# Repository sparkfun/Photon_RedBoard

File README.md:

SparkFun Photon RedBoard
========================================

[*SparkFun Photon RedBoard (DEV-13321)*](https://www.sparkfun.com/products/13321)

The SparkFun Photon RedBoard is a Particle Cloud-compatible WiFi development board. It can be programmed over-the-air, using Particle's Build IDE. It's like a Photon, but Arduino-shaped and red!

Repository Contents
-------------------

* **/Documentation** - Data sheets, additional product information
* **/Hardware** - Eagle design files (.brd, .sch)
* **/Production** - Production panel files (.brd)

Documentation
--------------
* **[Hookup Guide](https://learn.sparkfun.com/tutorials/photon-redboard-hookup-guide)** - Basic hookup guide for the SparkFun Photon RedBoard.
* **[Experiment Guide](https://learn.sparkfun.com/tutorials/photon-redboard-hookup-guide)** - Experiment guide for the SparkFun Photon RedBoard to send and receive data over WiFi.
* **[SparkFun Fritzing repo](https://github.com/sparkfun/Fritzing_Parts)** - Fritzing diagrams for SparkFun products.
* **[SparkFun 3D Model repo](https://github.com/sparkfun/3D_Models)** - 3D models of SparkFun products. 

Product Versions
----------------
* [DEV-13321](https://www.sparkfun.com/products/13321) - **Photon RedBoard**: Initial release of the SparkFun Photon RedBoard.
* [KIT-13320](https://www.sparkfun.com/products/13320) - **SparkFun Inventor's Kit for Photon**: A SparkFun Inventor's Kit based around the Photon RedBoard.

Version History
---------------
* [V_1.0](https://github.com/sparkfun/Photon_RedBoard/tree/V_1.0) - Initial hardware release - 1.0.

License Information
-------------------

This product is _**open source**_! 

Please review the LICENSE.md file for license information. 

If you have any questions or concerns on licensing, please contact techsupport@sparkfun.com.

Distributed as-is; no warranty is given.

- Your friends at SparkFun.

_<COLLABORATION CREDIT>_

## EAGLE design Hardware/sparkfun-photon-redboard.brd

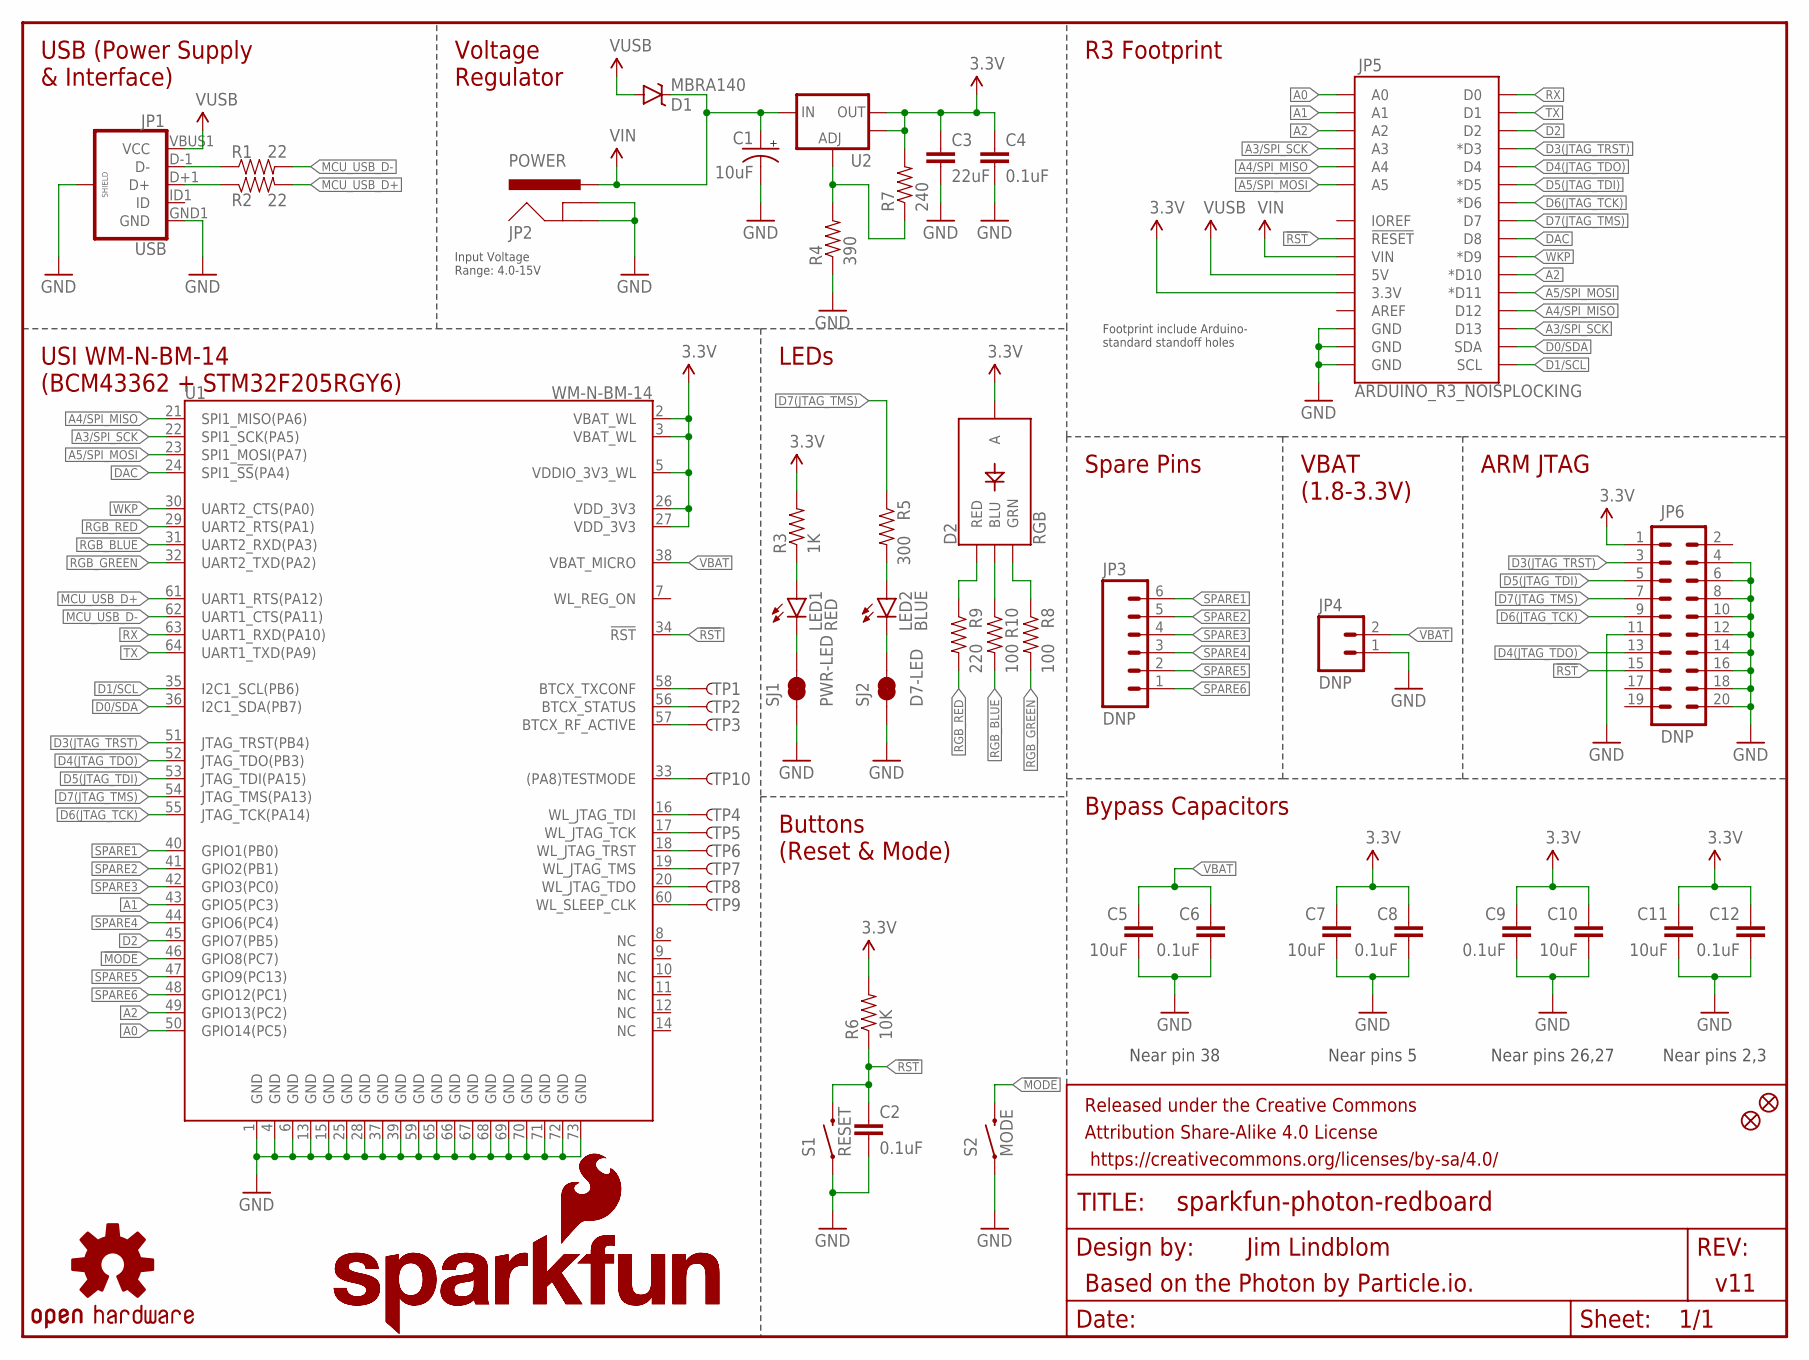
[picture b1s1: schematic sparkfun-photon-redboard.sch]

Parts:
C1: 10uF; EIA3216
C2, C4, C6, C8, C9, C12: 0.1uF; 0603-CAP
C3: 22uF; 0805
C5, C7, C10, C11: 10uF; 0603-CAP
D1: MBRA140; SMA-DIODE
D2: RGB; P-LCC-4-3
FID1, FID2: FIDUCIAL1X2; FIDUCIAL-1X2
FRAME1: FRAME-LETTER; CREATIVE_COMMONS
JP1: USB; USB-B-MICRO-SMD_V03
JP2: POWER; POWER_JACK_PTH_LOCK
JP3: DNP; 1X06
JP4: DNP; 1X02
JP5: ARDUINO_R3_NOISPLOCKING; ARDUINO_R3_NOISP_LOCKING
JP6: DNP; 2X10
LED1: RED; LED-1206
LED2: BLUE; LED-1206
LOGO1: OSHW-LOGOM; OSHW-LOGO-M
LOGO2: SFE_LOGO_NAME_FLAME.2_INCH; SFE_LOGO_NAME_FLAME_.2
LOGO3: SFE_LOGO_NAME_FLAME.4_INCH; SFE_LOGO_NAME_FLAME_.4
R1, R2: 22; 0603-RES
R3: 1K; 0603-RES
R4: 390; 0603-RES
R5: 300; 0603-RES
R6: 10K; 0603-RES
R7: 240; 0603-RES
R8: 100; 0603-RES
R9: 220; 0603
R10: 100; 0603
S1: RESET; TACTILE-PTH
S2: MODE; TACTILE-PTH
SJ1: PWR-LED; PAD-JUMPER-2-NC_BY_TRACE_YES_SILK
SJ2: D7-LED; PAD-JUMPER-2-NC_BY_TRACE_YES_SILK
TP1, TP2, TP3, TP4, TP5, TP6, TP7, TP8, TP9, TP10: TEST-POINTTP_15TH_THRU; TP_15TH
U1: WM-N-BM-14
U2: V_REG_LM1117SOT223; SOT223

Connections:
3.3V: C3.1, C4.1, C7.1, C8.1, C9.1, C10.1, C11.1, C12.1, D2.4 (A), JP5.3.3V, JP6.1, R3.2, R6.2, R7.2, U1.2 (VBAT_WL), U1.3 (VBAT_WL), U1.5 (VDDIO_3V3_WL), U1.26 (VDD_3V3), U1.27 (VDD_3V3), U2.2 (OUT), U2.4 (OUT)
!MODE: S2.3 (2), U1.46 (GPIO8(PC7))
!RST: C2.1, JP5.RESET@1 (!RESET!), JP6.15, R6.1, S1.3 (2), U1.34 (!RST!)
A0: JP5.A0, U1.50 (GPIO14(PC5))
A1: JP5.A1, U1.43 (GPIO5(PC3))
A2: JP5.A2, JP5.D10 (*D10), U1.49 (GPIO13(PC2))
A3/SPI_SCK: JP5.A3, JP5.D13, U1.22 (SPI1_SCK(PA5))
A4/SPI_MISO: JP5.A4, JP5.D12, U1.21 (SPI1_MISO(PA6))
A5/SPI_MOSI: JP5.A5, JP5.D11 (*D11), U1.23 (SPI1_MOSI(PA7))
BTCX_RF_ACTIVE: TP3.P$1, U1.57 (BTCX_RF_ACTIVE)
BTCX_STATUS: TP2.P$1, U1.56 (BTCX_STATUS)
BTCX_TXCONF: TP1.P$1, U1.58 (BTCX_TXCONF)
D0/SDA: JP5.SDA, U1.36 (I2C1_SDA(PB7))
D1/SCL: JP5.SCL, U1.35 (I2C1_SCL(PB6))
D2: JP5.D2, U1.45 (GPIO7(PB5))
D3(JTAG_TRST): JP5.D3 (*D3), JP6.3, U1.51 (JTAG_TRST(PB4))
D4(JTAG_TDO): JP5.D4, JP6.13, U1.52 (JTAG_TDO(PB3))
D5(JTAG_TDI): JP5.D5 (*D5), JP6.5, U1.53 (JTAG_TDI(PA15))
D6(JTAG_TCK): JP5.D6 (*D6), JP6.9, U1.55 (JTAG_TCK(PA14))
D7(JTAG_TMS): JP5.D7, JP6.7, R5.1, U1.54 (JTAG_TMS(PA13))
D+: JP1.D+1 (D+), R2.1
D-: JP1.D-1 (D-), R1.1
DAC: JP5.D8, U1.24 (SPI1_!SS!(PA4))
GND: C1.C (-), C2.2, C3.2, C4.2, C5.2, C6.2, C7.2, C8.2, C9.2, C10.2, C11.2, C12.2, JP1.GND1 (GND), JP1.SHIELD1 (SHIELD), JP1.SHIELD2 (SHIELD), JP1.SHIELD3 (SHIELD), JP2.GND, JP2.GNDBREAK, JP4.1, JP5.GND@1 (GND), JP5.GND@2 (GND), JP5.GND@3 (GND), JP6.4, JP6.6, JP6.8, JP6.10, JP6.11, JP6.12, JP6.14, JP6.16, JP6.18, JP6.20, R4.1, S1.1, S2.1, SJ1.1, SJ2.1, U1.1 (GND), U1.4 (GND), U1.6 (GND), U1.13 (GND), U1.15 (GND), U1.25 (GND), U1.28 (GND), U1.37 (GND), U1.39 (GND), U1.59 (GND), U1.65 (GND), U1.66 (GND), U1.67 (GND), U1.68 (GND), U1.69 (GND), U1.70 (GND), U1.71 (GND), U1.72 (GND), U1.73 (GND)
MCU_USB_D+: R2.2, U1.61 (UART1_RTS(PA12))
MCU_USB_D-: R1.2, U1.62 (UART1_CTS(PA11))
unnamed: TP10.P$1, U1.33 ((PA8)TESTMODE)
unnamed: LED1.C, SJ1.2
unnamed: D2.2 (GRN), R8.1
unnamed: D2.1 (RED), R9.1
unnamed: LED1.A, R3.1
unnamed: LED2.A, R5.2
unnamed: LED2.C, SJ2.2
unnamed: D2.3 (BLU), R10.1
unnamed: R4.2, R7.1, U2.1 (ADJ)
RGB_BLUE: R10.2, U1.31 (UART2_RXD(PA3))
RGB_GREEN: R8.2, U1.32 (UART2_TXD(PA2))
RGB_RED: R9.2, U1.29 (UART2_RTS(PA1))
RX: JP5.D0, U1.63 (UART1_RXD(PA10))
SPARE1: JP3.6, U1.40 (GPIO1(PB0))
SPARE2: JP3.5, U1.41 (GPIO2(PB1))
SPARE3: JP3.4, U1.42 (GPIO3(PC0))
SPARE4: JP3.3, U1.44 (GPIO6(PC4))
SPARE5: JP3.2, U1.47 (GPIO9(PC13))
SPARE6: JP3.1, U1.48 (GPIO12(PC1))
TX: JP5.D1, U1.64 (UART1_TXD(PA9))
VBAT: C5.1, C6.1, JP4.2, U1.38 (VBAT_MICRO)
VIN: C1.A (+), D1.C, JP2.PWR, JP5.VIN, U2.3 (IN)
VUSB: D1.A, JP1.VBUS1 (VCC), JP5.5V
WKP: JP5.D9 (*D9), U1.30 (UART2_CTS(PA0))
WL_JTAG_TCK: TP5.P$1, U1.17 (WL_JTAG_TCK)
WL_JTAG_TDI: TP4.P$1, U1.16 (WL_JTAG_TDI)
WL_JTAG_TDO: TP8.P$1, U1.20 (WL_JTAG_TDO)
WL_JTAG_TMS: TP7.P$1, U1.19 (WL_JTAG_TMS)
WL_JTAG_TRST: TP6.P$1, U1.18 (WL_JTAG_TRST)
WL_SLEEP_CLK: TP9.P$1, U1.60 (WL_SLEEP_CLK)

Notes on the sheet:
Near pin 38
Near pins 26,27
Near pins 5
Near pins 2,3
Voltage Regulator
USB (Power Supply & Interface)
R3 Footprint
Spare Pins
VBAT (1.8-3.3V)
ARM JTAG
Bypass Capacitors
LEDs
Buttons (Reset & Mode)
USI WM-N-BM-14 (BCM43362 + STM32F205RGY6)
Based on the Photon by Particle.io.
Jim Lindblom
v11
Input Voltage Range: 4.0-15V
Footprint include Arduino- standard standoff holes

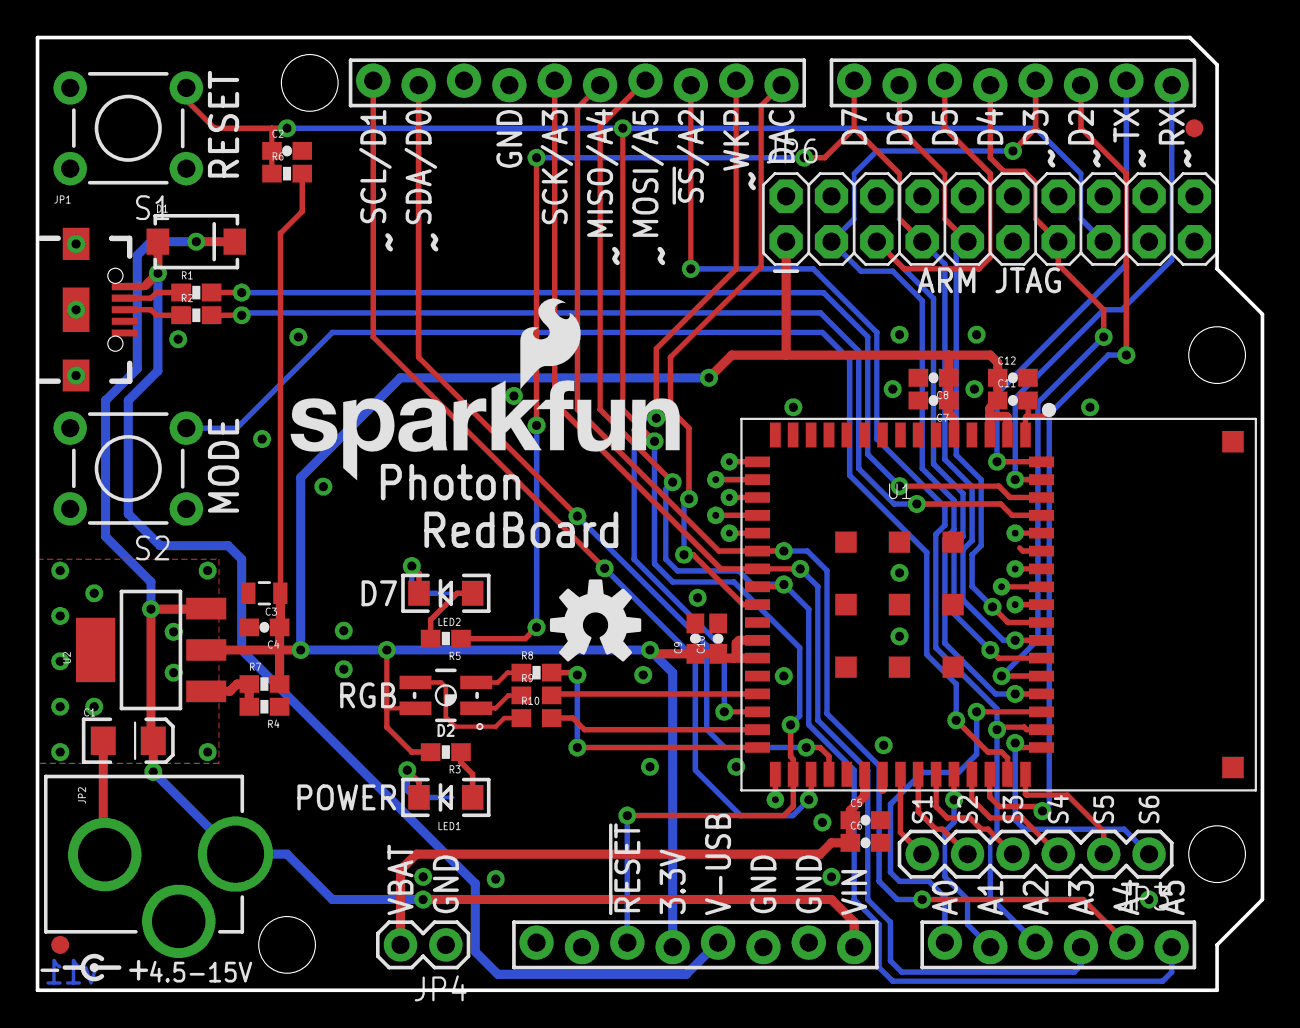
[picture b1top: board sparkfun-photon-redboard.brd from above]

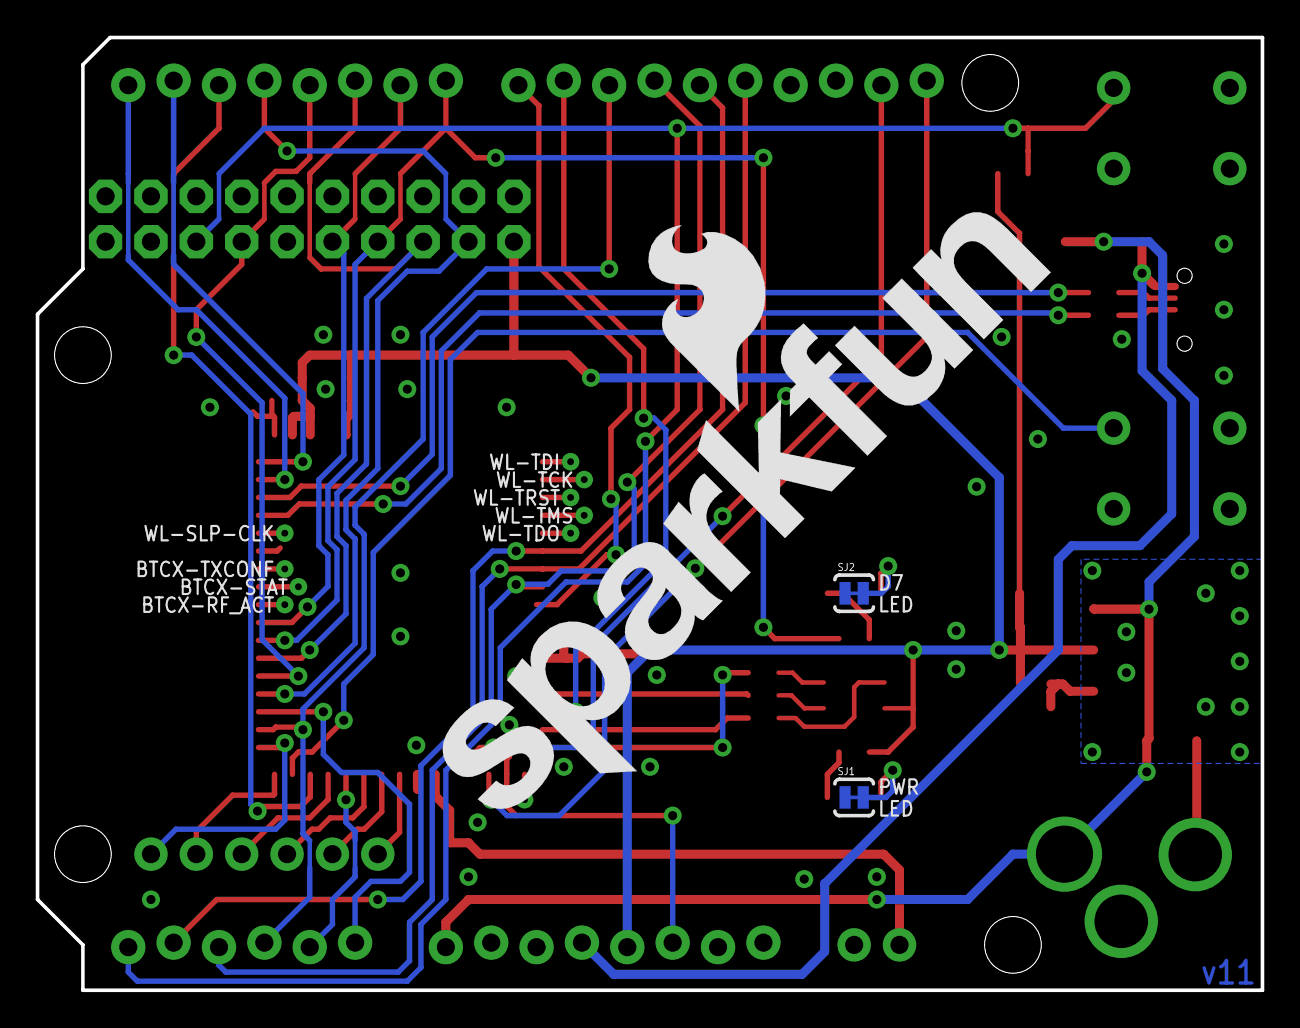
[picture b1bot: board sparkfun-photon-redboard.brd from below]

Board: 2 copper layers, 68.6 x 53.3 mm, 54 parts (3 on the bottom side), 56 nets.

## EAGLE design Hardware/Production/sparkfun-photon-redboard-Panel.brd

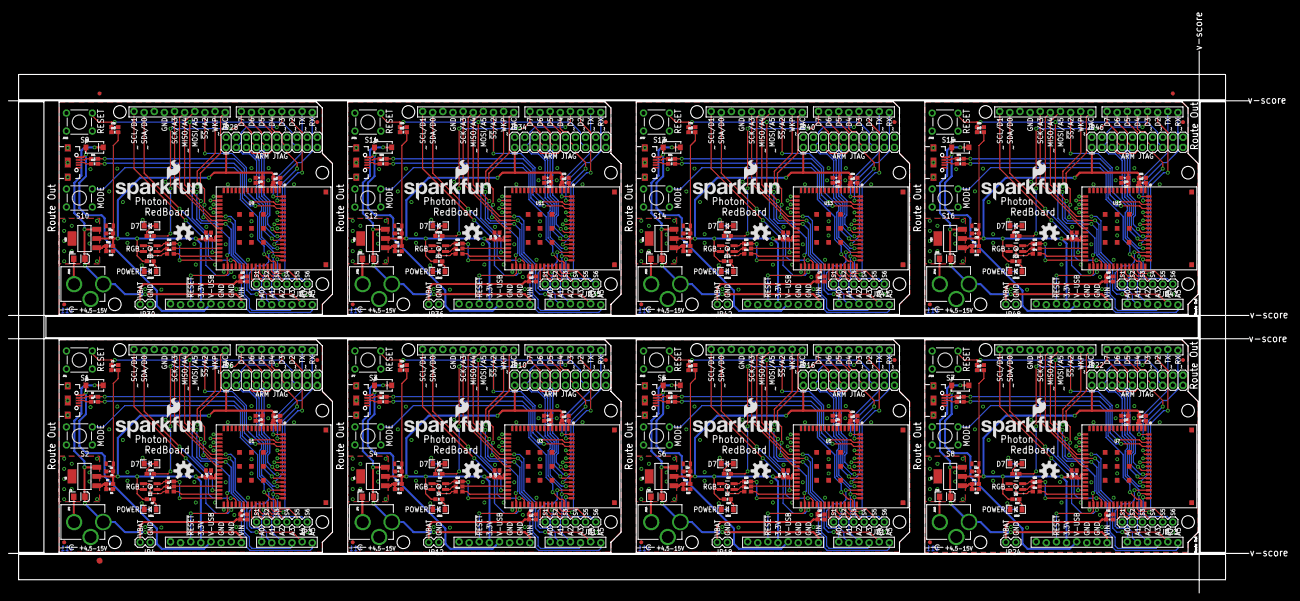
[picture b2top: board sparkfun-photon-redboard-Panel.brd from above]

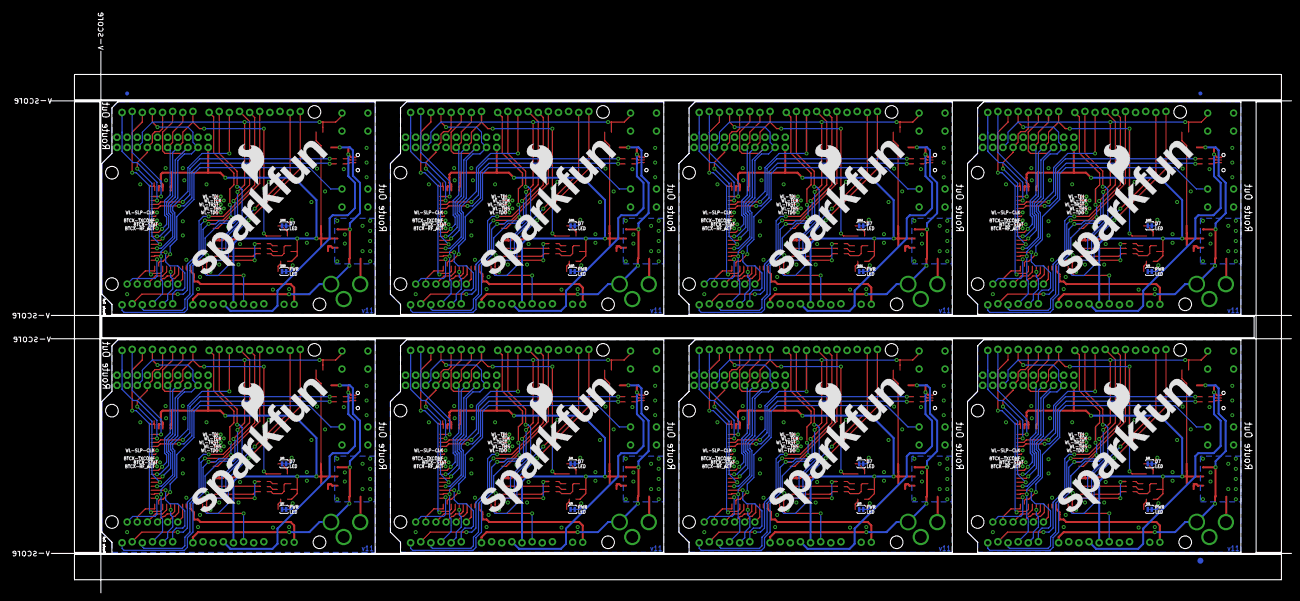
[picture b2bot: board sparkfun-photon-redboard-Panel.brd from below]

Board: 2 copper layers, 321.9 x 146.6 mm, 430 parts (27 on the bottom side), 448 nets.

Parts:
C1, C14, C26, C38, C50, C62, C74, C86: 10uF; EIA3216
C2, C4, C6, C8, C9, C12, C13, C16, C21, C22, C23, C24, C25, C28, C33, C34, C35, C36, C37, C40, C45, C46, C47, C48, C49, C52, C57, C58, C59, C60, C61, C64, C69, C70, C71, C72, C73, C76, C81, C82, C83, C84, C85, C88, C93, C94, C95, C96: 0.1uF; 0603-CAP
C3, C15, C27, C39, C51, C63, C75, C87: 22uF; 0805
C5, C7, C10, C11, C17, C18, C19, C20, C29, C30, C31, C32, C41, C42, C43, C44, C53, C54, C55, C56, C65, C66, C67, C68, C77, C78, C79, C80, C89, C90, C91, C92: 10uF; 0603-CAP
D1, D3, D5, D7, D9, D11, D13, D15: MBRA140; SMA-DIODE
D2, D4, D6, D8, D10, D12, D14, D16: RGB; P-LCC-4-3
E$1, E$2, E$3, E$4: FIDUCIAL-1X2
E$5, E$6: FIDUCIAL-1.5X3
FID1, FID2, FID3, FID4, FID5, FID6, FID7, FID8, FID9, FID10, FID11, FID12, FID13, FID14, FID15, FID16: FIDUCIAL1X2; FIDUCIAL-1X2
JP1, JP7, JP13, JP19, JP25, JP31, JP37, JP43: USB; USB-B-MICRO-SMD_V03
JP2, JP8, JP14, JP20, JP26, JP32, JP38, JP44: POWER; POWER_JACK_PTH_LOCK
JP3, JP11, JP17, JP23, JP29, JP35, JP41, JP47: DNP; 1X06
JP4, JP12, JP18, JP24, JP30, JP36, JP42, JP48: DNP; 1X02
JP5, JP9, JP15, JP21, JP27, JP33, JP39, JP45: ARDUINO_R3_NOISPLOCKING; ARDUINO_R3_NOISP_LOCKING
JP6, JP10, JP16, JP22, JP28, JP34, JP40, JP46: DNP; 2X10
LED1, LED4, LED6, LED8, LED10, LED12, LED14, LED16: RED; LED-1206
LED2, LED3, LED5, LED7, LED9, LED11, LED13, LED15: BLUE; LED-1206
LOGO1, LOGO5, LOGO8, LOGO11, LOGO14, LOGO17, LOGO20, LOGO23: OSHW-LOGOM; OSHW-LOGO-M
LOGO2, LOGO4, LOGO7, LOGO10, LOGO13, LOGO16, LOGO19, LOGO22: SFE_LOGO_NAME_FLAME.2_INCH; SFE_LOGO_NAME_FLAME_.2
LOGO3, LOGO6, LOGO9, LOGO12, LOGO15, LOGO18, LOGO21, LOGO24: SFE_LOGO_NAME_FLAME.4_INCH; SFE_LOGO_NAME_FLAME_.4
R1, R2, R11, R12, R21, R22, R31, R32, R41, R42, R51, R52, R61, R62, R71, R72: 22; 0603-RES
R3, R18, R28, R38, R48, R58, R68, R78: 1K; 0603-RES
R4, R19, R29, R39, R49, R59, R69, R79: 390; 0603-RES
R5, R17, R27, R37, R47, R57, R67, R77: 300; 0603-RES
R6, R13, R23, R33, R43, R53, R63, R73: 10K; 0603-RES
R7, R20, R30, R40, R50, R60, R70, R80: 240; 0603-RES
R8, R16, R26, R36, R46, R56, R66, R76: 100; 0603-RES
R9, R15, R25, R35, R45, R55, R65, R75: 220; 0603
R10, R14, R24, R34, R44, R54, R64, R74: 100; 0603
S1, S3, S5, S7, S9, S11, S13, S15: RESET; TACTILE-PTH
S2, S4, S6, S8, S10, S12, S14, S16: MODE; TACTILE-PTH
SJ1, SJ3, SJ5, SJ7, SJ9, SJ11, SJ13, SJ15: PWR-LED; PAD-JUMPER-2-NC_BY_TRACE_YES_SILK
SJ2, SJ4, SJ6, SJ8, SJ10, SJ12, SJ14, SJ16: D7-LED; PAD-JUMPER-2-NC_BY_TRACE_YES_SILK
TP1, TP2, TP3, TP4, TP5, TP6, TP7, TP8, TP9, TP10, TP11, TP12, TP13, TP14, TP15, TP16, TP17, TP18, TP19, TP20, TP21, TP22, TP23, TP24, TP25, TP26, TP27, TP28, TP29, TP30, TP31, TP32, TP33, TP34, TP35, TP36, TP37, TP38, TP39, TP40, TP41, TP42, TP43, TP44, TP45, TP46, TP47, TP48, TP49, TP50, TP51, TP52, TP53, TP54, TP55, TP56, TP57, TP58, TP59, TP60, TP61, TP62, TP63, TP64, TP65, TP66, TP67, TP68, TP69, TP70, TP71, TP72, TP73, TP74, TP75, TP76, TP77, TP78, TP79, TP80: TEST-POINTTP_15TH_THRU; TP_15TH
U1, U3, U5, U7, U9, U11, U13, U15: WM-N-BM-14
U2, U4, U6, U8, U10, U12, U14, U16: SOT223

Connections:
3.3V: C3.1, C4.1, C7.1, C8.1, C9.1, C10.1, C11.1, C12.1, D2.4, JP5.3.3V, JP6.1, R3.2, R6.2, R7.2, U1.2, U1.3, U1.5, U1.26, U1.27, U2.2, U2.4
3.3V1: C13.1, C15.1, C18.1, C19.1, C20.1, C22.1, C23.1, C24.1, D4.4, JP9.3.3V, JP10.1, R13.2, R18.2, R20.2, U3.2, U3.3, U3.5, U3.26, U3.27, U4.2, U4.4
3.3V2: C25.1, C27.1, C30.1, C31.1, C32.1, C34.1, C35.1, C36.1, D6.4, JP15.3.3V, JP16.1, R23.2, R28.2, R30.2, U5.2, U5.3, U5.5, U5.26, U5.27, U6.2, U6.4
3.3V3: C37.1, C39.1, C42.1, C43.1, C44.1, C46.1, C47.1, C48.1, D8.4, JP21.3.3V, JP22.1, R33.2, R38.2, R40.2, U7.2, U7.3, U7.5, U7.26, U7.27, U8.2, U8.4
3.3V4: C49.1, C51.1, C54.1, C55.1, C56.1, C58.1, C59.1, C60.1, D10.4, JP27.3.3V, JP28.1, R43.2, R48.2, R50.2, U9.2, U9.3, U9.5, U9.26, U9.27, U10.2, U10.4
3.3V5: C61.1, C63.1, C66.1, C67.1, C68.1, C70.1, C71.1, C72.1, D12.4, JP33.3.3V, JP34.1, R53.2, R58.2, R60.2, U11.2, U11.3, U11.5, U11.26, U11.27, U12.2, U12.4
3.3V6: C73.1, C75.1, C78.1, C79.1, C80.1, C82.1, C83.1, C84.1, D14.4, JP39.3.3V, JP40.1, R63.2, R68.2, R70.2, U13.2, U13.3, U13.5, U13.26, U13.27, U14.2, U14.4
3.3V7: C85.1, C87.1, C90.1, C91.1, C92.1, C94.1, C95.1, C96.1, D16.4, JP45.3.3V, JP46.1, R73.2, R78.2, R80.2, U15.2, U15.3, U15.5, U15.26, U15.27, U16.2, U16.4
!MODE: S2.3, U1.46
!MODE1: S4.3, U3.46
!MODE2: S6.3, U5.46
!MODE3: S8.3, U7.46
!MODE4: S10.3, U9.46
!MODE5: S12.3, U11.46
!MODE6: S14.3, U13.46
!MODE7: S16.3, U15.46
!RST: C2.1, JP5.RESET@1, JP6.15, R6.1, S1.3, U1.34
!RST1: C16.1, JP9.RESET@1, JP10.15, R13.1, S3.3, U3.34
!RST2: C28.1, JP15.RESET@1, JP16.15, R23.1, S5.3, U5.34
!RST3: C40.1, JP21.RESET@1, JP22.15, R33.1, S7.3, U7.34
!RST4: C52.1, JP27.RESET@1, JP28.15, R43.1, S9.3, U9.34
!RST5: C64.1, JP33.RESET@1, JP34.15, R53.1, S11.3, U11.34
!RST6: C76.1, JP39.RESET@1, JP40.15, R63.1, S13.3, U13.34
!RST7: C88.1, JP45.RESET@1, JP46.15, R73.1, S15.3, U15.34
A0: JP5.A0, U1.50
A1: JP5.A1, U1.43
A2: JP5.A2, JP5.D10, U1.49
A3: JP9.A2, JP9.D10, U3.49
A3/SPI_SCK: JP5.A3, JP5.D13, U1.22
A3/SPI_SCK1: JP9.A3, JP9.D13, U3.22
A3/SPI_SCK2: JP15.A3, JP15.D13, U5.22
A3/SPI_SCK3: JP21.A3, JP21.D13, U7.22
A3/SPI_SCK4: JP27.A3, JP27.D13, U9.22
A3/SPI_SCK5: JP33.A3, JP33.D13, U11.22
A3/SPI_SCK6: JP39.A3, JP39.D13, U13.22
A3/SPI_SCK7: JP45.A3, JP45.D13, U15.22
A4: JP9.A1, U3.43
A4/SPI_MISO: JP5.A4, JP5.D12, U1.21
A4/SPI_MISO1: JP9.A4, JP9.D12, U3.21
A4/SPI_MISO2: JP15.A4, JP15.D12, U5.21
A4/SPI_MISO3: JP21.A4, JP21.D12, U7.21
A4/SPI_MISO4: JP27.A4, JP27.D12, U9.21
A4/SPI_MISO5: JP33.A4, JP33.D12, U11.21
A4/SPI_MISO6: JP39.A4, JP39.D12, U13.21
A4/SPI_MISO7: JP45.A4, JP45.D12, U15.21
A5: JP9.A0, U3.50
A5/SPI_MOSI: JP5.A5, JP5.D11, U1.23
A5/SPI_MOSI1: JP9.A5, JP9.D11, U3.23
A5/SPI_MOSI2: JP15.A5, JP15.D11, U5.23
A5/SPI_MOSI3: JP21.A5, JP21.D11, U7.23
A5/SPI_MOSI4: JP27.A5, JP27.D11, U9.23
A5/SPI_MOSI5: JP33.A5, JP33.D11, U11.23
A5/SPI_MOSI6: JP39.A5, JP39.D11, U13.23
A5/SPI_MOSI7: JP45.A5, JP45.D11, U15.23
A6: JP15.A2, JP15.D10, U5.49
A7: JP15.A1, U5.43
A8: JP15.A0, U5.50
A9: JP21.A2, JP21.D10, U7.49
A10: JP21.A1, U7.43
A11: JP21.A0, U7.50
A12: JP27.A2, JP27.D10, U9.49
A13: JP27.A1, U9.43
A14: JP27.A0, U9.50
A15: JP33.A2, JP33.D10, U11.49
A16: JP33.A1, U11.43
A17: JP33.A0, U11.50
A18: JP39.A2, JP39.D10, U13.49
A19: JP39.A1, U13.43
A20: JP39.A0, U13.50
A21: JP45.A2, JP45.D10, U15.49
A22: JP45.A1, U15.43
A23: JP45.A0, U15.50
BTCX_RF_ACTIVE: TP3.P$1, U1.57
BTCX_RF_ACTIVE1: TP11.P$1, U3.57
BTCX_RF_ACTIVE2: TP21.P$1, U5.57
BTCX_RF_ACTIVE3: TP31.P$1, U7.57
BTCX_RF_ACTIVE4: TP41.P$1, U9.57
BTCX_RF_ACTIVE5: TP51.P$1, U11.57
BTCX_RF_ACTIVE6: TP61.P$1, U13.57
BTCX_RF_ACTIVE7: TP71.P$1, U15.57
BTCX_STATUS: TP2.P$1, U1.56
BTCX_STATUS1: TP13.P$1, U3.56
BTCX_STATUS2: TP23.P$1, U5.56
BTCX_STATUS3: TP33.P$1, U7.56
BTCX_STATUS4: TP43.P$1, U9.56
BTCX_STATUS5: TP53.P$1, U11.56
BTCX_STATUS6: TP63.P$1, U13.56
BTCX_STATUS7: TP73.P$1, U15.56
BTCX_TXCONF: TP1.P$1, U1.58
BTCX_TXCONF1: TP12.P$1, U3.58
BTCX_TXCONF2: TP22.P$1, U5.58
BTCX_TXCONF3: TP32.P$1, U7.58
BTCX_TXCONF4: TP42.P$1, U9.58
BTCX_TXCONF5: TP52.P$1, U11.58
BTCX_TXCONF6: TP62.P$1, U13.58
BTCX_TXCONF7: TP72.P$1, U15.58
D0/SDA: JP5.SDA, U1.36
D0/SDA1: JP9.SDA, U3.36
D0/SDA2: JP15.SDA, U5.36
D0/SDA3: JP21.SDA, U7.36
D0/SDA4: JP27.SDA, U9.36
D0/SDA5: JP33.SDA, U11.36
D0/SDA6: JP39.SDA, U13.36
D0/SDA7: JP45.SDA, U15.36
D1: JP9.D2, U3.45
D1/SCL: JP5.SCL, U1.35
D1/SCL1: JP9.SCL, U3.35
D1/SCL2: JP15.SCL, U5.35
D1/SCL3: JP21.SCL, U7.35
D1/SCL4: JP27.SCL, U9.35
D1/SCL5: JP33.SCL, U11.35
D1/SCL6: JP39.SCL, U13.35
D1/SCL7: JP45.SCL, U15.35
D2: JP5.D2, U1.45
D3: JP15.D2, U5.45
D3(JTAG_TRST): JP5.D3, JP6.3, U1.51
D3(JTAG_TRST)1: JP9.D3, JP10.3, U3.51
D3(JTAG_TRST)2: JP15.D3, JP16.3, U5.51
D3(JTAG_TRST)3: JP21.D3, JP22.3, U7.51
D3(JTAG_TRST)4: JP27.D3, JP28.3, U9.51
D3(JTAG_TRST)5: JP33.D3, JP34.3, U11.51
D3(JTAG_TRST)6: JP39.D3, JP40.3, U13.51
D3(JTAG_TRST)7: JP45.D3, JP46.3, U15.51
D4: JP21.D2, U7.45
D4(JTAG_TDO): JP5.D4, JP6.13, U1.52
D4(JTAG_TDO)1: JP9.D4, JP10.13, U3.52
D4(JTAG_TDO)2: JP15.D4, JP16.13, U5.52
D4(JTAG_TDO)3: JP21.D4, JP22.13, U7.52
D4(JTAG_TDO)4: JP27.D4, JP28.13, U9.52
D4(JTAG_TDO)5: JP33.D4, JP34.13, U11.52
D4(JTAG_TDO)6: JP39.D4, JP40.13, U13.52
D4(JTAG_TDO)7: JP45.D4, JP46.13, U15.52
D5: JP27.D2, U9.45
D5(JTAG_TDI): JP5.D5, JP6.5, U1.53
D5(JTAG_TDI)1: JP9.D5, JP10.5, U3.53
D5(JTAG_TDI)2: JP15.D5, JP16.5, U5.53
D5(JTAG_TDI)3: JP21.D5, JP22.5, U7.53
D5(JTAG_TDI)4: JP27.D5, JP28.5, U9.53
D5(JTAG_TDI)5: JP33.D5, JP34.5, U11.53
D5(JTAG_TDI)6: JP39.D5, JP40.5, U13.53
D5(JTAG_TDI)7: JP45.D5, JP46.5, U15.53
D6: JP33.D2, U11.45
D6(JTAG_TCK): JP5.D6, JP6.9, U1.55
D6(JTAG_TCK)1: JP9.D6, JP10.9, U3.55
D6(JTAG_TCK)2: JP15.D6, JP16.9, U5.55
D6(JTAG_TCK)3: JP21.D6, JP22.9, U7.55
D6(JTAG_TCK)4: JP27.D6, JP28.9, U9.55
D6(JTAG_TCK)5: JP33.D6, JP34.9, U11.55
D6(JTAG_TCK)6: JP39.D6, JP40.9, U13.55
D6(JTAG_TCK)7: JP45.D6, JP46.9, U15.55
D7: JP39.D2, U13.45
D7(JTAG_TMS): JP5.D7, JP6.7, R5.1, U1.54
D7(JTAG_TMS)1: JP9.D7, JP10.7, R17.1, U3.54
D7(JTAG_TMS)2: JP15.D7, JP16.7, R27.1, U5.54
D7(JTAG_TMS)3: JP21.D7, JP22.7, R37.1, U7.54
D7(JTAG_TMS)4: JP27.D7, JP28.7, R47.1, U9.54
D7(JTAG_TMS)5: JP33.D7, JP34.7, R57.1, U11.54
D7(JTAG_TMS)6: JP39.D7, JP40.7, R67.1, U13.54
D7(JTAG_TMS)7: JP45.D7, JP46.7, R77.1, U15.54
D8: JP45.D2, U15.45
D+: JP1.D+1, R2.1
D+1: JP7.D+1, R12.1
D+2: JP13.D+1, R22.1
D+3: JP19.D+1, R32.1
D+4: JP25.D+1, R42.1
D+5: JP31.D+1, R52.1
D+6: JP37.D+1, R62.1
D+7: JP43.D+1, R72.1
D-: JP1.D-1, R1.1
D-1: JP7.D-1, R11.1
D-2: JP13.D-1, R21.1
D-3: JP19.D-1, R31.1
D-4: JP25.D-1, R41.1
D-5: JP31.D-1, R51.1
D-6: JP37.D-1, R61.1
D-7: JP43.D-1, R71.1
DAC: JP5.D8, U1.24
DAC1: JP9.D8, U3.24
DAC2: JP15.D8, U5.24
DAC3: JP21.D8, U7.24
DAC4: JP27.D8, U9.24
DAC5: JP33.D8, U11.24
DAC6: JP39.D8, U13.24
DAC7: JP45.D8, U15.24
GND: C1.C, C2.2, C3.2, C4.2, C5.2, C6.2, C7.2, C8.2, C9.2, C10.2, C11.2, C12.2, JP1.GND1, JP1.SHIELD1, JP1.SHIELD2, JP1.SHIELD3, JP2.GND, JP2.GNDBREAK, JP4.1, JP5.GND@1, JP5.GND@2, JP5.GND@3, JP6.4, JP6.6, JP6.8, JP6.10, JP6.11, JP6.12, JP6.14, JP6.16, JP6.18, JP6.20, R4.1, S1.1, S2.1, SJ1.1, SJ2.1, U1.1, U1.4, U1.6, U1.13, U1.15, U1.25, U1.28, U1.37, U1.39, U1.59, U1.65, U1.66, U1.67, U1.68, U1.69, U1.70, U1.71, U1.72, U1.73
GND1: C13.2, C14.C, C15.2, C16.2, C17.2, C18.2, C19.2, C20.2, C21.2, C22.2, C23.2, C24.2, JP7.GND1, JP7.SHIELD1, JP7.SHIELD2, JP7.SHIELD3, JP8.GND, JP8.GNDBREAK, JP9.GND@1, JP9.GND@2, JP9.GND@3, JP10.4, JP10.6, JP10.8, JP10.10, JP10.11, JP10.12, JP10.14, JP10.16, JP10.18, JP10.20, JP12.1, R19.1, S3.1, S4.1, SJ3.1, SJ4.1, U3.1, U3.4, U3.6, U3.13, U3.15, U3.25, U3.28, U3.37, U3.39, U3.59, U3.65, U3.66, U3.67, U3.68, U3.69, U3.70, U3.71, U3.72, U3.73
GND2: C25.2, C26.C, C27.2, C28.2, C29.2, C30.2, C31.2, C32.2, C33.2, C34.2, C35.2, C36.2, JP13.GND1, JP13.SHIELD1, JP13.SHIELD2, JP13.SHIELD3, JP14.GND, JP14.GNDBREAK, JP15.GND@1, JP15.GND@2, JP15.GND@3, JP16.4, JP16.6, JP16.8, JP16.10, JP16.11, JP16.12, JP16.14, JP16.16, JP16.18, JP16.20, JP18.1, R29.1, S5.1, S6.1, SJ5.1, SJ6.1, U5.1, U5.4, U5.6, U5.13, U5.15, U5.25, U5.28, U5.37, U5.39, U5.59, U5.65, U5.66, U5.67, U5.68, U5.69, U5.70, U5.71, U5.72, U5.73
GND3: C37.2, C38.C, C39.2, C40.2, C41.2, C42.2, C43.2, C44.2, C45.2, C46.2, C47.2, C48.2, JP19.GND1, JP19.SHIELD1, JP19.SHIELD2, JP19.SHIELD3, JP20.GND, JP20.GNDBREAK, JP21.GND@1, JP21.GND@2, JP21.GND@3, JP22.4, JP22.6, JP22.8, JP22.10, JP22.11, JP22.12, JP22.14, JP22.16, JP22.18, JP22.20, JP24.1, R39.1, S7.1, S8.1, SJ7.1, SJ8.1, U7.1, U7.4, U7.6, U7.13, U7.15, U7.25, U7.28, U7.37, U7.39, U7.59, U7.65, U7.66, U7.67, U7.68, U7.69, U7.70, U7.71, U7.72, U7.73
GND4: C49.2, C50.C, C51.2, C52.2, C53.2, C54.2, C55.2, C56.2, C57.2, C58.2, C59.2, C60.2, JP25.GND1, JP25.SHIELD1, JP25.SHIELD2, JP25.SHIELD3, JP26.GND, JP26.GNDBREAK, JP27.GND@1, JP27.GND@2, JP27.GND@3, JP28.4, JP28.6, JP28.8, JP28.10, JP28.11, JP28.12, JP28.14, JP28.16, JP28.18, JP28.20, JP30.1, R49.1, S9.1, S10.1, SJ9.1, SJ10.1, U9.1, U9.4, U9.6, U9.13, U9.15, U9.25, U9.28, U9.37, U9.39, U9.59, U9.65, U9.66, U9.67, U9.68, U9.69, U9.70, U9.71, U9.72, U9.73
GND5: C61.2, C62.C, C63.2, C64.2, C65.2, C66.2, C67.2, C68.2, C69.2, C70.2, C71.2, C72.2, JP31.GND1, JP31.SHIELD1, JP31.SHIELD2, JP31.SHIELD3, JP32.GND, JP32.GNDBREAK, JP33.GND@1, JP33.GND@2, JP33.GND@3, JP34.4, JP34.6, JP34.8, JP34.10, JP34.11, JP34.12, JP34.14, JP34.16, JP34.18, JP34.20, JP36.1, R59.1, S11.1, S12.1, SJ11.1, SJ12.1, U11.1, U11.4, U11.6, U11.13, U11.15, U11.25, U11.28, U11.37, U11.39, U11.59, U11.65, U11.66, U11.67, U11.68, U11.69, U11.70, U11.71, U11.72, U11.73
GND6: C73.2, C74.C, C75.2, C76.2, C77.2, C78.2, C79.2, C80.2, C81.2, C82.2, C83.2, C84.2, JP37.GND1, JP37.SHIELD1, JP37.SHIELD2, JP37.SHIELD3, JP38.GND, JP38.GNDBREAK, JP39.GND@1, JP39.GND@2, JP39.GND@3, JP40.4, JP40.6, JP40.8, JP40.10, JP40.11, JP40.12, JP40.14, JP40.16, JP40.18, JP40.20, JP42.1, R69.1, S13.1, S14.1, SJ13.1, SJ14.1, U13.1, U13.4, U13.6, U13.13, U13.15, U13.25, U13.28, U13.37, U13.39, U13.59, U13.65, U13.66, U13.67, U13.68, U13.69, U13.70, U13.71, U13.72, U13.73
GND7: C85.2, C86.C, C87.2, C88.2, C89.2, C90.2, C91.2, C92.2, C93.2, C94.2, C95.2, C96.2, JP43.GND1, JP43.SHIELD1, JP43.SHIELD2, JP43.SHIELD3, JP44.GND, JP44.GNDBREAK, JP45.GND@1, JP45.GND@2, JP45.GND@3, JP46.4, JP46.6, JP46.8, JP46.10, JP46.11, JP46.12, JP46.14, JP46.16, JP46.18, JP46.20, JP48.1, R79.1, S15.1, S16.1, SJ15.1, SJ16.1, U15.1, U15.4, U15.6, U15.13, U15.15, U15.25, U15.28, U15.37, U15.39, U15.59, U15.65, U15.66, U15.67, U15.68, U15.69, U15.70, U15.71, U15.72, U15.73
MCU_USB_D+: R2.2, U1.61
MCU_USB_D+1: R12.2, U3.61
MCU_USB_D+2: R22.2, U5.61
MCU_USB_D+3: R32.2, U7.61
MCU_USB_D+4: R42.2, U9.61
MCU_USB_D+5: R52.2, U11.61
MCU_USB_D+6: R62.2, U13.61
MCU_USB_D+7: R72.2, U15.61
MCU_USB_D-: R1.2, U1.62
MCU_USB_D-1: R11.2, U3.62
MCU_USB_D-2: R21.2, U5.62
MCU_USB_D-3: R31.2, U7.62
MCU_USB_D-4: R41.2, U9.62
MCU_USB_D-5: R51.2, U11.62
MCU_USB_D-6: R61.2, U13.62
MCU_USB_D-7: R71.2, U15.62
unnamed: TP10.P$1, U1.33
unnamed: LED1.C, SJ1.2
unnamed: D2.2, R8.1
unnamed: D2.1, R9.1
unnamed: R19.2, R20.1, U4.1
unnamed: LED1.A, R3.1
unnamed: LED2.A, R5.2
unnamed: LED2.C, SJ2.2
unnamed: D2.3, R10.1
unnamed: D4.2, R16.1
unnamed: D4.1, R15.1
unnamed: LED3.A, R17.2
unnamed: LED4.A, R18.1
unnamed: TP20.P$1, U3.33
unnamed: R4.2, R7.1, U2.1
unnamed: LED4.C, SJ3.2
unnamed: LED3.C, SJ4.2
unnamed: D4.3, R14.1
unnamed: R29.2, R30.1, U6.1
unnamed: D6.2, R26.1
unnamed: D6.1, R25.1
unnamed: LED5.A, R27.2
unnamed: LED6.A, R28.1
unnamed: TP30.P$1, U5.33
unnamed: LED6.C, SJ5.2
unnamed: LED5.C, SJ6.2
unnamed: D6.3, R24.1
unnamed: R39.2, R40.1, U8.1
unnamed: D8.2, R36.1
unnamed: D8.1, R35.1
unnamed: LED7.A, R37.2
unnamed: LED8.A, R38.1
unnamed: TP40.P$1, U7.33
unnamed: LED8.C, SJ7.2
unnamed: LED7.C, SJ8.2
unnamed: D8.3, R34.1
unnamed: R49.2, R50.1, U10.1
unnamed: D10.2, R46.1
unnamed: D10.1, R45.1
unnamed: LED9.A, R47.2
unnamed: LED10.A, R48.1
unnamed: TP50.P$1, U9.33
unnamed: LED10.C, SJ9.2
unnamed: LED9.C, SJ10.2
unnamed: D10.3, R44.1
unnamed: R59.2, R60.1, U12.1
unnamed: D12.2, R56.1
unnamed: D12.1, R55.1
unnamed: LED11.A, R57.2
unnamed: LED12.A, R58.1
unnamed: TP60.P$1, U11.33
unnamed: LED12.C, SJ11.2
unnamed: LED11.C, SJ12.2
unnamed: D12.3, R54.1
unnamed: R69.2, R70.1, U14.1
unnamed: D14.2, R66.1
unnamed: D14.1, R65.1
unnamed: LED13.A, R67.2
unnamed: LED14.A, R68.1
unnamed: TP70.P$1, U13.33
unnamed: LED14.C, SJ13.2
unnamed: LED13.C, SJ14.2
unnamed: D14.3, R64.1
unnamed: R79.2, R80.1, U16.1
unnamed: D16.2, R76.1
unnamed: D16.1, R75.1
unnamed: LED15.A, R77.2
unnamed: LED16.A, R78.1
unnamed: TP80.P$1, U15.33
unnamed: LED16.C, SJ15.2
unnamed: LED15.C, SJ16.2
unnamed: D16.3, R74.1
RGB_BLUE: R10.2, U1.31
RGB_BLUE1: R14.2, U3.31
RGB_BLUE2: R24.2, U5.31
RGB_BLUE3: R34.2, U7.31
RGB_BLUE4: R44.2, U9.31
RGB_BLUE5: R54.2, U11.31
RGB_BLUE6: R64.2, U13.31
RGB_BLUE7: R74.2, U15.31
RGB_GREEN: R8.2, U1.32
RGB_GREEN1: R16.2, U3.32
RGB_GREEN2: R26.2, U5.32
RGB_GREEN3: R36.2, U7.32
RGB_GREEN4: R46.2, U9.32
RGB_GREEN5: R56.2, U11.32
RGB_GREEN6: R66.2, U13.32
RGB_GREEN7: R76.2, U15.32
RGB_RED: R9.2, U1.29
RGB_RED1: R15.2, U3.29
RGB_RED2: R25.2, U5.29
RGB_RED3: R35.2, U7.29
RGB_RED4: R45.2, U9.29
RGB_RED5: R55.2, U11.29
RGB_RED6: R65.2, U13.29
RGB_RED7: R75.2, U15.29
RX: JP5.D0, U1.63
RX1: JP9.D0, U3.63
RX2: JP15.D0, U5.63
RX3: JP21.D0, U7.63
RX4: JP27.D0, U9.63
RX5: JP33.D0, U11.63
RX6: JP39.D0, U13.63
RX7: JP45.D0, U15.63
SPARE1: JP3.6, U1.40
SPARE2: JP3.5, U1.41
SPARE3: JP3.4, U1.42
SPARE4: JP3.3, U1.44
SPARE5: JP3.2, U1.47
SPARE6: JP3.1, U1.48
SPARE7: JP11.6, U3.40
SPARE8: JP11.5, U3.41
SPARE9: JP11.4, U3.42
SPARE10: JP11.3, U3.44
SPARE11: JP11.2, U3.47
SPARE12: JP11.1, U3.48
SPARE13: JP17.6, U5.40
SPARE14: JP17.5, U5.41
SPARE15: JP17.4, U5.42
SPARE16: JP17.3, U5.44
SPARE17: JP17.2, U5.47
SPARE18: JP17.1, U5.48
SPARE19: JP23.6, U7.40
SPARE20: JP23.5, U7.41
SPARE21: JP23.4, U7.42
SPARE22: JP23.3, U7.44
SPARE23: JP23.2, U7.47
SPARE24: JP23.1, U7.48
SPARE25: JP29.6, U9.40
SPARE26: JP29.5, U9.41
SPARE27: JP29.4, U9.42
SPARE28: JP29.3, U9.44
SPARE29: JP29.2, U9.47
SPARE30: JP29.1, U9.48
SPARE31: JP35.6, U11.40
SPARE32: JP35.5, U11.41
SPARE33: JP35.4, U11.42
SPARE34: JP35.3, U11.44
SPARE35: JP35.2, U11.47
SPARE36: JP35.1, U11.48
SPARE37: JP41.6, U13.40
SPARE38: JP41.5, U13.41
SPARE39: JP41.4, U13.42
SPARE40: JP41.3, U13.44
SPARE41: JP41.2, U13.47
SPARE42: JP41.1, U13.48
SPARE43: JP47.6, U15.40
SPARE44: JP47.5, U15.41
SPARE45: JP47.4, U15.42
SPARE46: JP47.3, U15.44
SPARE47: JP47.2, U15.47
SPARE48: JP47.1, U15.48
TX: JP5.D1, U1.64
TX1: JP9.D1, U3.64
TX2: JP15.D1, U5.64
TX3: JP21.D1, U7.64
TX4: JP27.D1, U9.64
TX5: JP33.D1, U11.64
TX6: JP39.D1, U13.64
TX7: JP45.D1, U15.64
VBAT: C5.1, C6.1, JP4.2, U1.38
VBAT1: C17.1, C21.1, JP12.2, U3.38
VBAT2: C29.1, C33.1, JP18.2, U5.38
VBAT3: C41.1, C45.1, JP24.2, U7.38
VBAT4: C53.1, C57.1, JP30.2, U9.38
VBAT5: C65.1, C69.1, JP36.2, U11.38
VBAT6: C77.1, C81.1, JP42.2, U13.38
VBAT7: C89.1, C93.1, JP48.2, U15.38
VIN: C1.A, D1.C, JP2.PWR, JP5.VIN, U2.3
VIN1: C14.A, D3.C, JP8.PWR, JP9.VIN, U4.3
VIN2: C26.A, D5.C, JP14.PWR, JP15.VIN, U6.3
VIN3: C38.A, D7.C, JP20.PWR, JP21.VIN, U8.3
VIN4: C50.A, D9.C, JP26.PWR, JP27.VIN, U10.3
VIN5: C62.A, D11.C, JP32.PWR, JP33.VIN, U12.3
VIN6: C74.A, D13.C, JP38.PWR, JP39.VIN, U14.3
VIN7: C86.A, D15.C, JP44.PWR, JP45.VIN, U16.3
VUSB: D1.A, JP1.VBUS1, JP5.5V
VUSB1: D3.A, JP7.VBUS1, JP9.5V
VUSB2: D5.A, JP13.VBUS1, JP15.5V
VUSB3: D7.A, JP19.VBUS1, JP21.5V
VUSB4: D9.A, JP25.VBUS1, JP27.5V
VUSB5: D11.A, JP31.VBUS1, JP33.5V
VUSB6: D13.A, JP37.VBUS1, JP39.5V
VUSB7: D15.A, JP43.VBUS1, JP45.5V
WKP: JP5.D9, U1.30
WKP1: JP9.D9, U3.30
WKP2: JP15.D9, U5.30
WKP3: JP21.D9, U7.30
WKP4: JP27.D9, U9.30
WKP5: JP33.D9, U11.30
WKP6: JP39.D9, U13.30
WKP7: JP45.D9, U15.30
WL_JTAG_TCK: TP5.P$1, U1.17
WL_JTAG_TCK1: TP15.P$1, U3.17
WL_JTAG_TCK2: TP25.P$1, U5.17
WL_JTAG_TCK3: TP35.P$1, U7.17
WL_JTAG_TCK4: TP45.P$1, U9.17
WL_JTAG_TCK5: TP55.P$1, U11.17
WL_JTAG_TCK6: TP65.P$1, U13.17
WL_JTAG_TCK7: TP75.P$1, U15.17
WL_JTAG_TDI: TP4.P$1, U1.16
WL_JTAG_TDI1: TP14.P$1, U3.16
WL_JTAG_TDI2: TP24.P$1, U5.16
WL_JTAG_TDI3: TP34.P$1, U7.16
WL_JTAG_TDI4: TP44.P$1, U9.16
WL_JTAG_TDI5: TP54.P$1, U11.16
WL_JTAG_TDI6: TP64.P$1, U13.16
WL_JTAG_TDI7: TP74.P$1, U15.16
WL_JTAG_TDO: TP8.P$1, U1.20
WL_JTAG_TDO1: TP18.P$1, U3.20
WL_JTAG_TDO2: TP28.P$1, U5.20
WL_JTAG_TDO3: TP38.P$1, U7.20
WL_JTAG_TDO4: TP48.P$1, U9.20
WL_JTAG_TDO5: TP58.P$1, U11.20
WL_JTAG_TDO6: TP68.P$1, U13.20
WL_JTAG_TDO7: TP78.P$1, U15.20
WL_JTAG_TMS: TP7.P$1, U1.19
WL_JTAG_TMS1: TP17.P$1, U3.19
WL_JTAG_TMS2: TP27.P$1, U5.19
WL_JTAG_TMS3: TP37.P$1, U7.19
WL_JTAG_TMS4: TP47.P$1, U9.19
WL_JTAG_TMS5: TP57.P$1, U11.19
WL_JTAG_TMS6: TP67.P$1, U13.19
WL_JTAG_TMS7: TP77.P$1, U15.19
WL_JTAG_TRST: TP6.P$1, U1.18
WL_JTAG_TRST1: TP16.P$1, U3.18
WL_JTAG_TRST2: TP26.P$1, U5.18
WL_JTAG_TRST3: TP36.P$1, U7.18
WL_JTAG_TRST4: TP46.P$1, U9.18
WL_JTAG_TRST5: TP56.P$1, U11.18
WL_JTAG_TRST6: TP66.P$1, U13.18
WL_JTAG_TRST7: TP76.P$1, U15.18
WL_SLEEP_CLK: TP9.P$1, U1.60
WL_SLEEP_CLK1: TP19.P$1, U3.60
WL_SLEEP_CLK2: TP29.P$1, U5.60
WL_SLEEP_CLK3: TP39.P$1, U7.60
WL_SLEEP_CLK4: TP49.P$1, U9.60
WL_SLEEP_CLK5: TP59.P$1, U11.60
WL_SLEEP_CLK6: TP69.P$1, U13.60
WL_SLEEP_CLK7: TP79.P$1, U15.60

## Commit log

2015-03-09 Initial commit of hardware.
2015-03-09 Adding PROD_ID to USB connector.
2015-03-10 Added measurements. Re-routed corner pins, moved JP3 away from standoff.
2015-03-10 Moving silk indicator on P1. Labeling RGB LED. Re-routing some grounds.
2015-03-10 Fixing tiny airwire.
2015-03-12 Moving a few vias for a more complete ground plane. Adjusting some silk.
2015-04-03 Swap WKP & RGB red signals. Add tp's to WL JTAG.
2015-06-05 Swapping PA1 and PA0 (Red RGB and WKP pins).
2015-06-05 Renaming extra pins to S1-S6 (SPARE).
2015-06-05 Adding jumper to disconnect Power LED.
2015-06-05 Changing Arduino headers to locking footprints.
2015-06-30 Tweaking some silkscreen
    - Changing DAC to "DAC/A6"
    - Moving board name silk.
2015-07-10 Adding jumper to disconnect D7 LED.
2015-07-10 Swapping WKP and DAC pins (maps PWM better).
2015-07-10 Moving vias to avoid silk.
2015-07-17 Cleaning up VIN trace.
2015-07-22 created panel v10
2015-08-26 Renaming files to match new directory name.
2015-08-26 Adding v10 schematic pdf.
2015-08-26 Fixing up the readme real nice-like.
2017-05-09 Photon Redboard with New USB Connector
2017-05-11 Updated USB package
2017-05-11 Updated USB part
2017-05-12 Updated RedBoard with new PTH USB
2017-06-01 Updated USB Package + Approved DRC errors
2017-08-04 Updated Revision to 2.0 for Reds
2017-08-04 Approved DRC errors
2017-08-21 panel
2021-06-18 Switched RGB LED and resistor values
    -Previous RGB was EOL
    -changed resistor values to match existing proven designs (100/100/220)
2021-06-18 updated version to "v11" in bottom copper and sch
2021-06-23 panelized v11 for production
    -note, I also fixed the testpoint so it is exposed on the bottom side (correctly).
2021-06-28 Revised panel
2021-06-29 added "route out" text to far right side cut out areas of panel
2021-06-29 removing old production panel brd, re-naming latest gerber zip with v11

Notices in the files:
parts and their libraries:
SparkFun-Capacitors: Licensing: Creative Commons ShareAlike 4.0 International - https://creativecommons.org/licenses/by-sa/4.0
SparkFun-Aesthetics: Released under the Creative Commons Attribution Share-Alike 4.0 License
SparkFun-Aesthetics: https://creativecommons.org/licenses/by-sa/4.0
